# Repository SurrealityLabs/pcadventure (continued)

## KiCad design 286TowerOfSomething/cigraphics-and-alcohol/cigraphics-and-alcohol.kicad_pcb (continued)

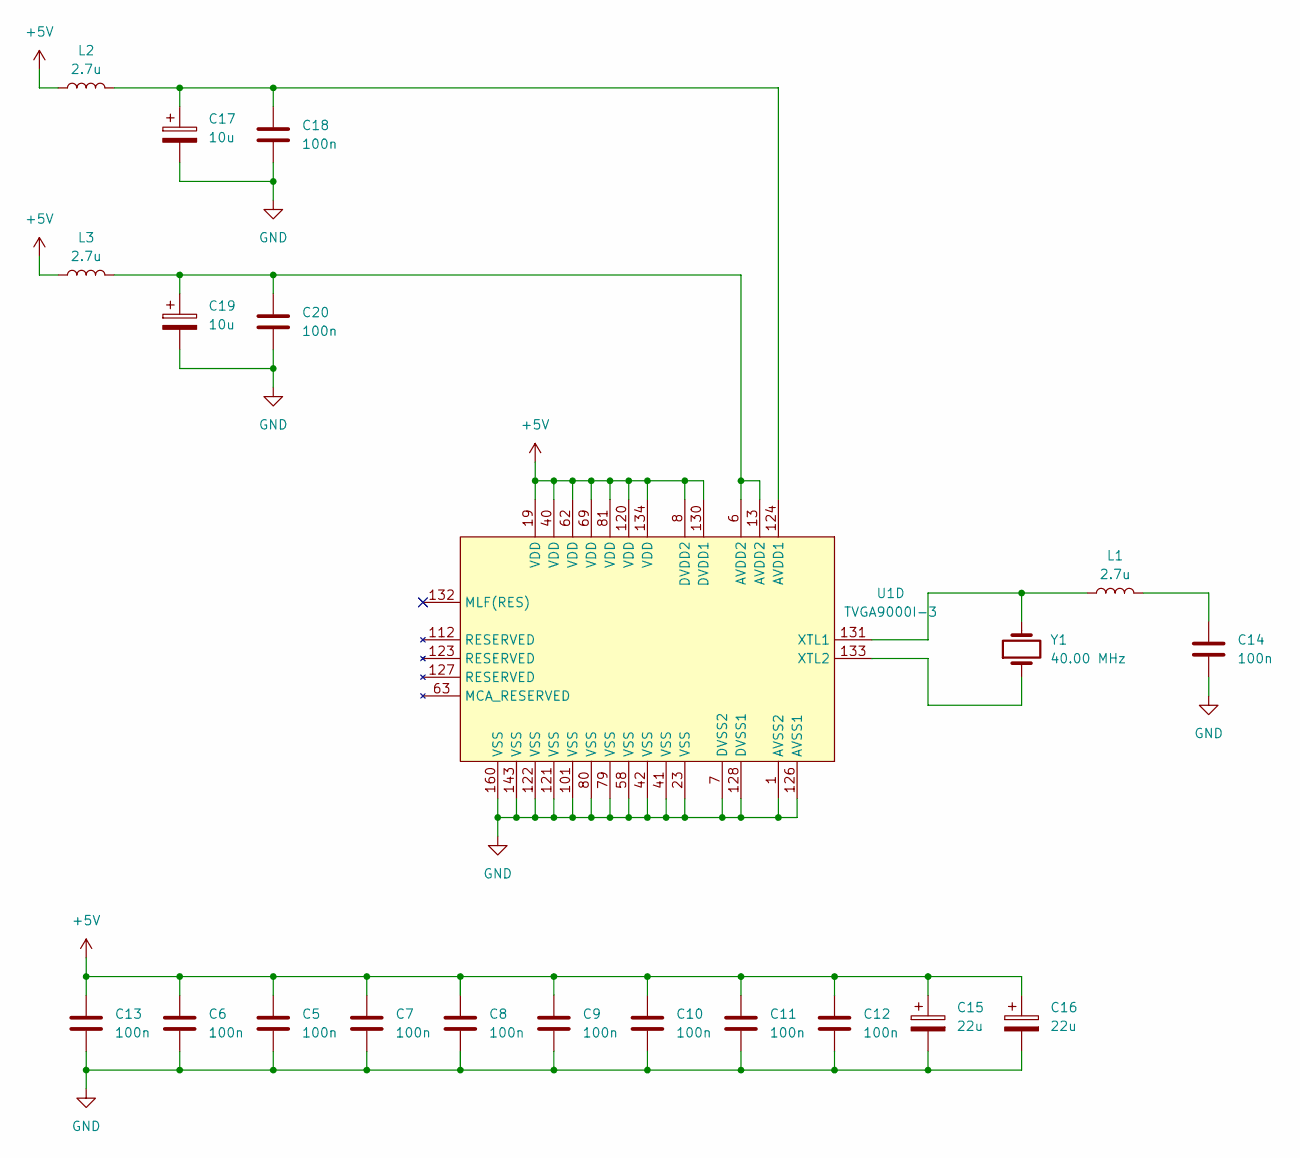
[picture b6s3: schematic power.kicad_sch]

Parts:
C5, C6, C7, C8, C9, C10, C11, C12, C13, C14, C18, C20: 100n; C_0603_1608Metric_Pad1.08x0.95mm_HandSolder
C15, C16: 22u; CP_Elec_5x5.3
C17, C19: 10u; CP_Elec_5x5.3
L1, L2, L3: 2.7u; L_0603_1608Metric_Pad1.05x0.95mm_HandSolder
U1: TVGA9000I-3; PQFP-160_28x28mm_P0.65mm
Y1: 40.00 MHz

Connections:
+5V: C5.1, C6.1, C7.1, C8.1, C9.1, C10.1, C11.1, C12.1, C13.1, C15.1, C16.1, L2.1, L3.1, U1.8 (DVDD2), U1.19 (VDD), U1.40 (VDD), U1.62 (VDD), U1.69 (VDD), U1.81 (VDD), U1.120 (VDD), U1.130 (DVDD1), U1.134 (VDD); also elsewhere on the board
GND: C5.2, C6.2, C7.2, C8.2, C9.2, C10.2, C11.2, C12.2, C13.2, C14.2, C15.2, C16.2, C17.2, C18.2, C19.2, C20.2, U1.1 (AVSS2), U1.7 (DVSS2), U1.23 (VSS), U1.41 (VSS), U1.42 (VSS), U1.58 (VSS), U1.79 (VSS), U1.80 (VSS), U1.101 (VSS), U1.121 (VSS), U1.122 (VSS), U1.126 (AVSS1), U1.128 (DVSS1), U1.143 (VSS), U1.160 (VSS); also elsewhere on the board
unnamed: C14.1, L1.2
unnamed: C19.1, C20.1, L3.2, U1.6 (AVDD2), U1.13 (AVDD2)
unnamed: C17.1, C18.1, L2.2, U1.124 (AVDD1)
unnamed: L1.1, U1.131 (XTL1), Y1.2
unnamed: U1.133 (XTL2), Y1.1

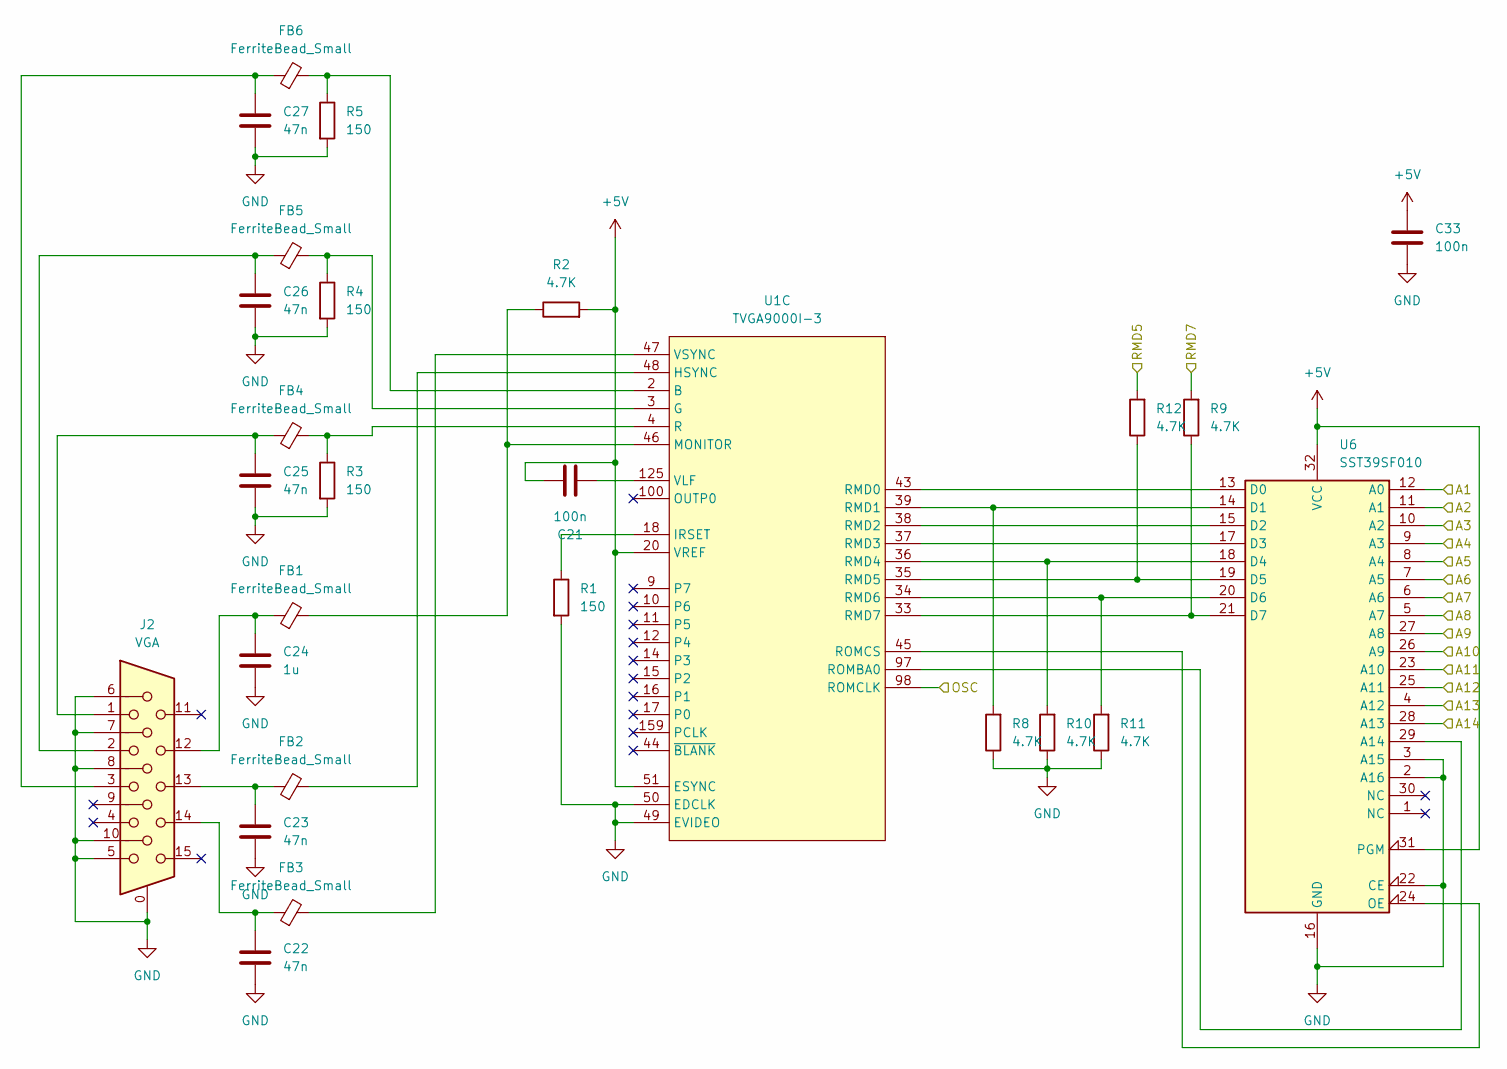
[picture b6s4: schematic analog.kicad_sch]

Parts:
C21, C33: 100n; C_0603_1608Metric_Pad1.08x0.95mm_HandSolder
C22, C23, C25, C26, C27: 47n; C_0603_1608Metric_Pad1.08x0.95mm_HandSolder
C24: 1u; C_0603_1608Metric_Pad1.08x0.95mm_HandSolder
FB1, FB2, FB3, FB4, FB5, FB6: FerriteBead_Small; L_0603_1608Metric_Pad1.05x0.95mm_HandSolder
J2: VGA; DSUB-15-HD_Female_Horizontal_P2.29x1.90mm_EdgePinOffset3.03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
R1, R3, R4, R5: 150; R_0603_1608Metric_Pad0.98x0.95mm_HandSolder
R2, R8, R9, R10, R11, R12: 4.7K; R_0603_1608Metric_Pad0.98x0.95mm_HandSolder
U1: TVGA9000I-3; PQFP-160_28x28mm_P0.65mm
U6: SST39SF010; DIP-32_W15.24mm

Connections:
+5V: C21.2, C33.1, R2.2, U1.20 (VREF), U1.51 (ESYNC), U6.31 (PGM), U6.32 (VCC); also elsewhere on the board
/A1: U6.12 (A0); also elsewhere on the board
/A2: U6.11 (A1); also elsewhere on the board
/A3: U6.10 (A2); also elsewhere on the board
/A4: U6.9 (A3); also elsewhere on the board
/A5: U6.8 (A4); also elsewhere on the board
/A6: U6.7 (A5); also elsewhere on the board
/A7: U6.6 (A6); also elsewhere on the board
/A8: U6.5 (A7); also elsewhere on the board
/A9: U6.27 (A8); also elsewhere on the board
/A10: U6.26 (A9); also elsewhere on the board
/A11: U6.23 (A10); also elsewhere on the board
/A12: U6.25 (A11); also elsewhere on the board
/A13: U6.4 (A12); also elsewhere on the board
/A14: U6.28 (A13); also elsewhere on the board
/Analog/RMD5: R12.2; also elsewhere on the board
/Analog/RMD7: R9.2; also elsewhere on the board
/OSC: U1.98 (ROMCLK); also elsewhere on the board
GND: C22.2, C23.2, C24.2, C25.2, C26.2, C27.2, C33.2, J2.0, J2.5, J2.6, J2.7, J2.8, J2.10, R1.2, R3.2, R4.2, R5.2, R8.1, R10.1, R11.1, U1.49 (EVIDEO), U1.50 (EDCLK), U6.2 (A16), U6.3 (A15), U6.16 (GND), U6.22 (CE); also elsewhere on the board
unnamed: C22.1, FB3.1, J2.14
unnamed: C23.1, FB2.1, J2.13
unnamed: C24.1, FB1.1, J2.12
unnamed: C25.1, FB4.1, J2.1
unnamed: C26.1, FB5.1, J2.2
unnamed: C27.1, FB6.1, J2.3
unnamed: FB6.2, R5.1, U1.2 (B)
unnamed: FB5.2, R4.1, U1.3 (G)
unnamed: FB2.2, U1.48 (HSYNC)
unnamed: R1.1, U1.18 (IRSET)
unnamed: FB1.2, R2.1, U1.46 (MONITOR)
unnamed: FB4.2, R3.1, U1.4 (R)
unnamed: U1.43 (RMD0), U6.13 (D0)
unnamed: R8.2, U1.39 (RMD1), U6.14 (D1)
unnamed: U1.38 (RMD2), U6.15 (D2)
unnamed: U1.37 (RMD3), U6.17 (D3)
unnamed: R10.2, U1.36 (RMD4), U6.18 (D4)
unnamed: R12.1, U1.35 (RMD5), U6.19 (D5)
unnamed: R11.2, U1.34 (RMD6), U6.20 (D6)
unnamed: R9.1, U1.33 (RMD7), U6.21 (D7)
unnamed: U1.97 (ROMBA0), U6.29 (A14)
unnamed: U1.45 (ROMCS), U6.24 (OE)
unnamed: C21.1, U1.125 (VLF)
unnamed: FB3.2, U1.47 (VSYNC)

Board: 2 copper layers, 70 parts (0 on the bottom side), 130 nets, no tracks yet.

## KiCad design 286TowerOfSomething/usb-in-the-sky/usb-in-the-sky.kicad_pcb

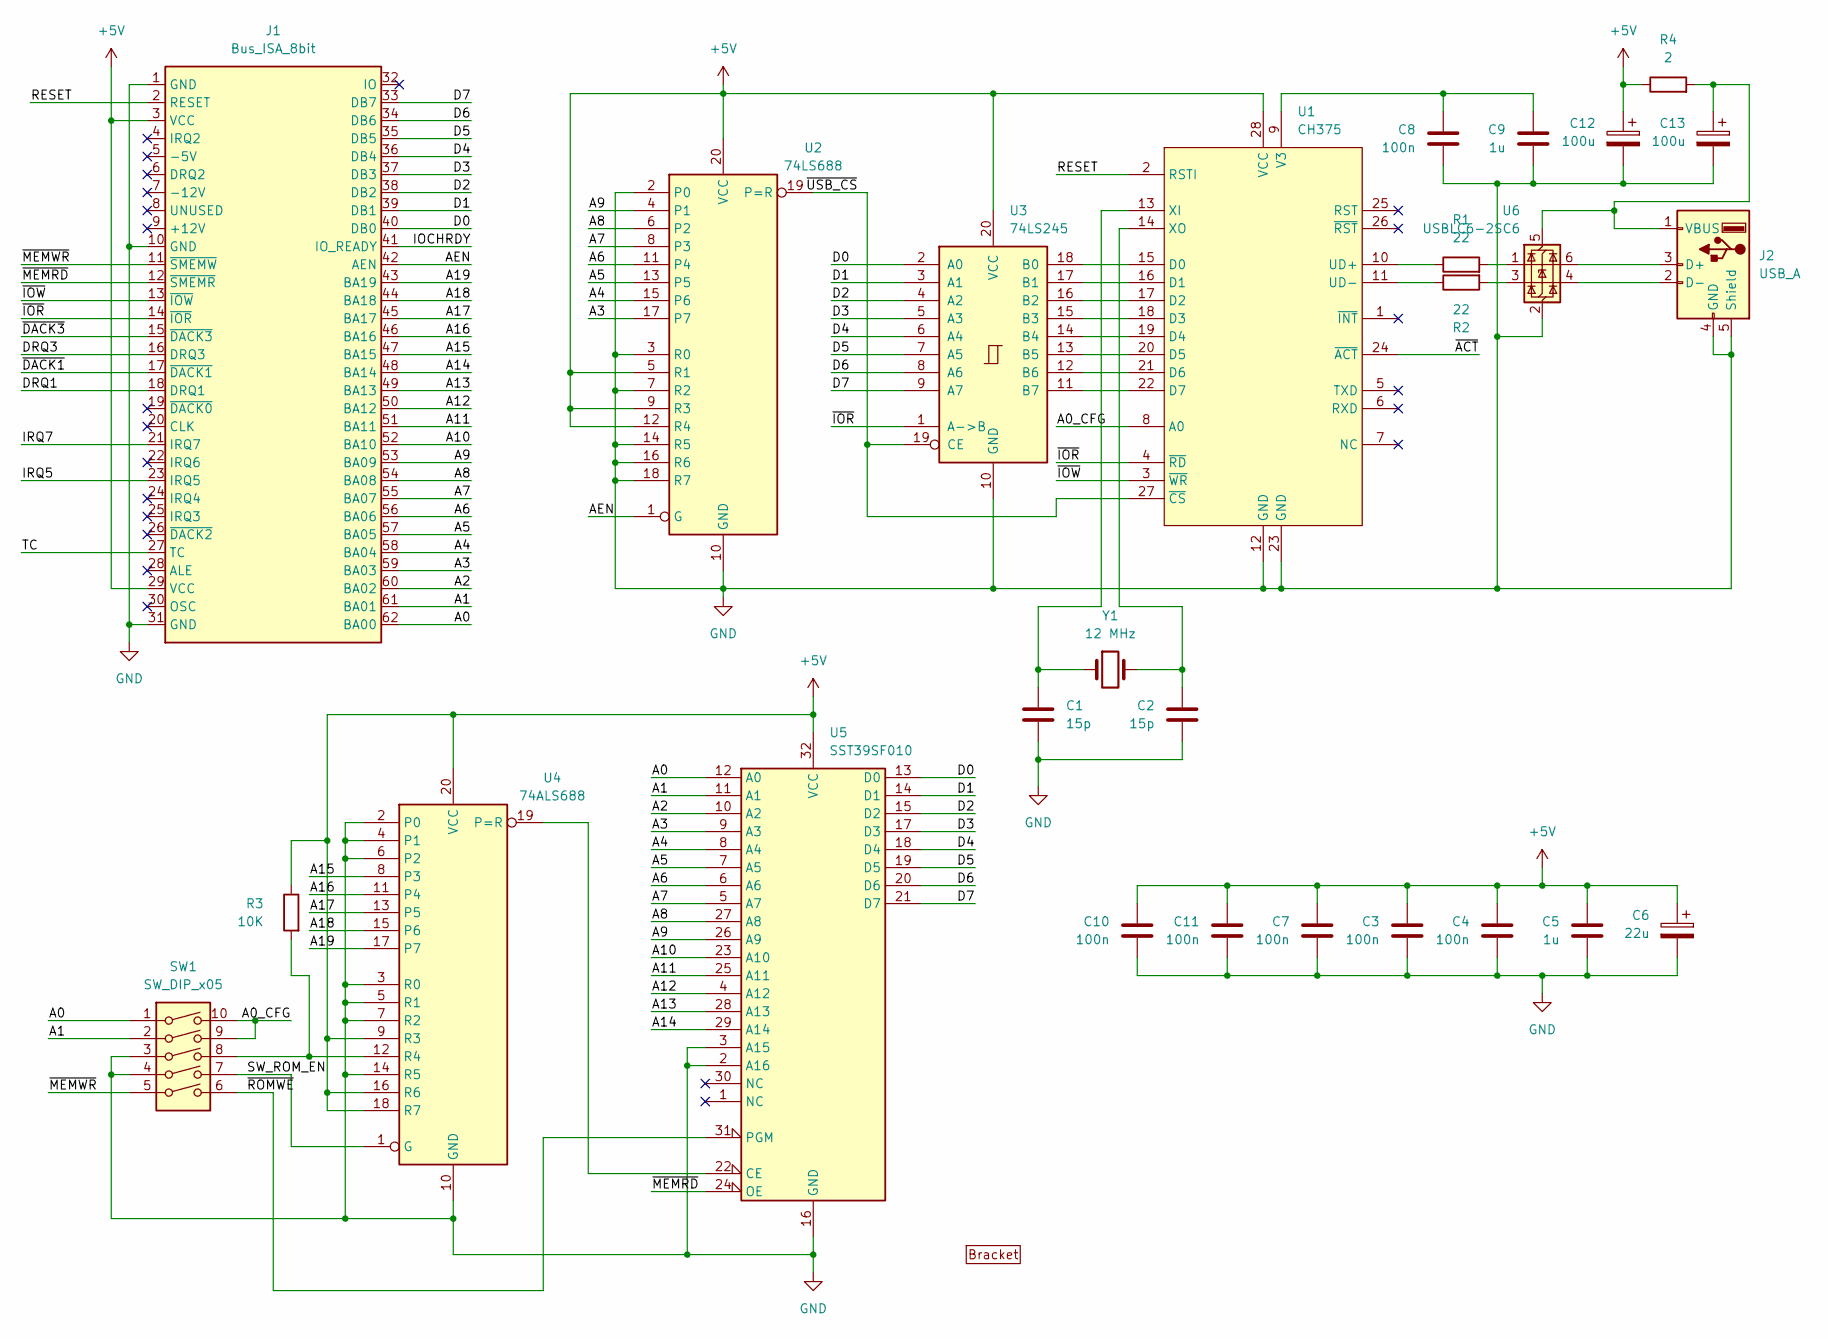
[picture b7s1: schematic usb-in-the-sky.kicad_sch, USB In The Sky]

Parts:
BRACKET1: PC_BRACKET_ISA_KEYSTONE_9200_Rev1_1
C1, C2: 15p; C_0603_1608Metric_Pad1.08x0.95mm_HandSolder
C3, C4, C7, C8, C10, C11: 100n; C_0603_1608Metric_Pad1.08x0.95mm_HandSolder
C5, C9: 1u; C_0805_2012Metric_Pad1.18x1.45mm_HandSolder
C6: 22u; CP_Elec_5x5.3
C12, C13: 100u; CP_Elec_5x5.3
J1: Bus_ISA_8bit; BUS_AT_8BIT
J2: USB_A; USB_A_Stewart_SS-52100-001_Horizontal
R1, R2: 22; R_0603_1608Metric_Pad0.98x0.95mm_HandSolder
R3: 10K; R_0603_1608Metric_Pad0.98x0.95mm_HandSolder
R4: 2; R_0603_1608Metric_Pad0.98x0.95mm_HandSolder
SW1: SW_DIP_x05; SW_DIP_SPSTx05_Slide_9.78x14.88mm_W7.62mm_P2.54mm
U1: CH375; SOP-28_8.4x18.16mm_P1.27mm
U2: 74LS688; DIP-20_W7.62mm
U3: 74LS245; DIP-20_W7.62mm
U4: 74ALS688; DIP-20_W7.62mm
U5: SST39SF010; DIP-32_W15.24mm
U6: USBLC6-2SC6; SOT-23-6
Y1: 12 MHz; Crystal_HC49-U_Vertical

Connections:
+5V: C3.1, C4.1, C5.1, C6.1, C7.1, C10.1, C11.1, C12.1, J1.3 (VCC), J1.29 (VCC), R3.1, R4.1, U1.28 (VCC), U2.5 (R1), U2.9 (R3), U2.12 (R4), U2.20 (VCC), U3.20 (VCC), U4.9 (R3), U4.16 (R6), U4.18 (R7), U4.20 (VCC), U5.32 (VCC)
/A0: J1.62 (BA00), SW1.1, U5.12 (A0)
/A0_CFG: SW1.9, SW1.10, U1.8 (A0)
/A1: J1.61 (BA01), SW1.2, U5.11 (A1)
/A2: J1.60 (BA02), U5.10 (A2)
/A3: J1.59 (BA03), U2.17 (P7), U5.9 (A3)
/A4: J1.58 (BA04), U2.15 (P6), U5.8 (A4)
/A5: J1.57 (BA05), U2.13 (P5), U5.7 (A5)
/A6: J1.56 (BA06), U2.11 (P4), U5.6 (A6)
/A7: J1.55 (BA07), U2.8 (P3), U5.5 (A7)
/A8: J1.54 (BA08), U2.6 (P2), U5.27 (A8)
/A9: J1.53 (BA09), U2.4 (P1), U5.26 (A9)
/A10: J1.52 (BA10), U5.23 (A10)
/A11: J1.51 (BA11), U5.25 (A11)
/A12: J1.50 (BA12), U5.4 (A12)
/A13: J1.49 (BA13), U5.28 (A13)
/A14: J1.48 (BA14), U5.29 (A14)
/A15: J1.47 (BA15), U4.8 (P3)
/A16: J1.46 (BA16), U4.11 (P4)
/A17: J1.45 (BA17), U4.13 (P5)
/A18: J1.44 (BA18), U4.15 (P6)
/A19: J1.43 (BA19), U4.17 (P7)
/AEN: J1.42 (AEN), U2.1 (G)
/D0: J1.40 (DB0), U3.2 (A0), U5.13 (D0)
/D1: J1.39 (DB1), U3.3 (A1), U5.14 (D1)
/D2: J1.38 (DB2), U3.4 (A2), U5.15 (D2)
/D3: J1.37 (DB3), U3.5 (A3), U5.17 (D3)
/D4: J1.36 (DB4), U3.6 (A4), U5.18 (D4)
/D5: J1.35 (DB5), U3.7 (A5), U5.19 (D5)
/D6: J1.34 (DB6), U3.8 (A6), U5.20 (D6)
/D7: J1.33 (DB7), U3.9 (A7), U5.21 (D7)
/DRQ1: J1.18 (DRQ1)
/DRQ3: J1.16 (DRQ3)
/IOCHRDY: J1.41 (IO_READY)
/IRQ5: J1.23 (IRQ5)
/IRQ7: J1.21 (IRQ7)
/RESET: J1.2 (RESET), U1.2 (RSTI)
/SW_ROM_EN: SW1.7, U4.1 (G)
/TC: J1.27 (TC)
/~ACT: U1.24 (~ACT)
/~DACK1: J1.17 (~DACK1)
/~DACK3: J1.15 (~DACK3)
/~IOR: J1.14 (~IOR), U1.4 (~RD), U3.1 (A->B)
/~IOW: J1.13 (~IOW), U1.3 (~WR)
/~MEMRD: J1.12 (~SMEMR), U5.24 (OE)
/~MEMWR: J1.11 (~SMEMW), SW1.5
/~ROMWE: SW1.6, U5.31 (PGM)
/~USB_CS: U1.27 (~CS), U2.19 (P=R), U3.19 (CE)
GND: C1.2, C2.2, C3.2, C4.2, C5.2, C6.2, C7.2, C8.2, C9.2, C10.2, C11.2, C12.2, C13.2, J1.1 (GND), J1.10 (GND), J1.31 (GND), J2.4 (GND), J2.5 (Shield), SW1.3, SW1.4, U1.12 (GND), U1.23 (GND), U2.2 (P0), U2.3 (R0), U2.7 (R2), U2.10 (GND), U2.14 (R5), U2.16 (R6), U2.18 (R7), U3.10 (GND), U4.2 (P0), U4.3 (R0), U4.4 (P1), U4.5 (R1), U4.6 (P2), U4.7 (R2), U4.10 (GND), U4.14 (R5), U5.2 (A16), U5.3 (A15), U5.16 (GND), U6.2 (GND)
unnamed: J2.3 (D+), U6.6 (I/O1)
unnamed: J2.2 (D-), U6.4 (I/O2)
unnamed: C13.1, J2.1 (VBUS), R4.2, U6.5 (VBUS)
unnamed: R1.2, U6.1 (I/O1)
unnamed: R2.2, U6.3 (I/O2)
unnamed: U1.15 (D0), U3.18 (B0)
unnamed: U1.16 (D1), U3.17 (B1)
unnamed: U1.17 (D2), U3.16 (B2)
unnamed: U1.18 (D3), U3.15 (B3)
unnamed: U1.19 (D4), U3.14 (B4)
unnamed: U1.20 (D5), U3.13 (B5)
unnamed: U1.21 (D6), U3.12 (B6)
unnamed: U1.22 (D7), U3.11 (B7)
unnamed: R1.1, U1.10 (UD+)
unnamed: R2.1, U1.11 (UD-)
unnamed: C8.1, C9.1, U1.9 (V3)
unnamed: C1.1, U1.13 (XI), Y1.1
unnamed: C2.1, U1.14 (XO), Y1.2
unnamed: U4.19 (P=R), U5.22 (CE)
unnamed: R3.2, SW1.8, U4.12 (R4)

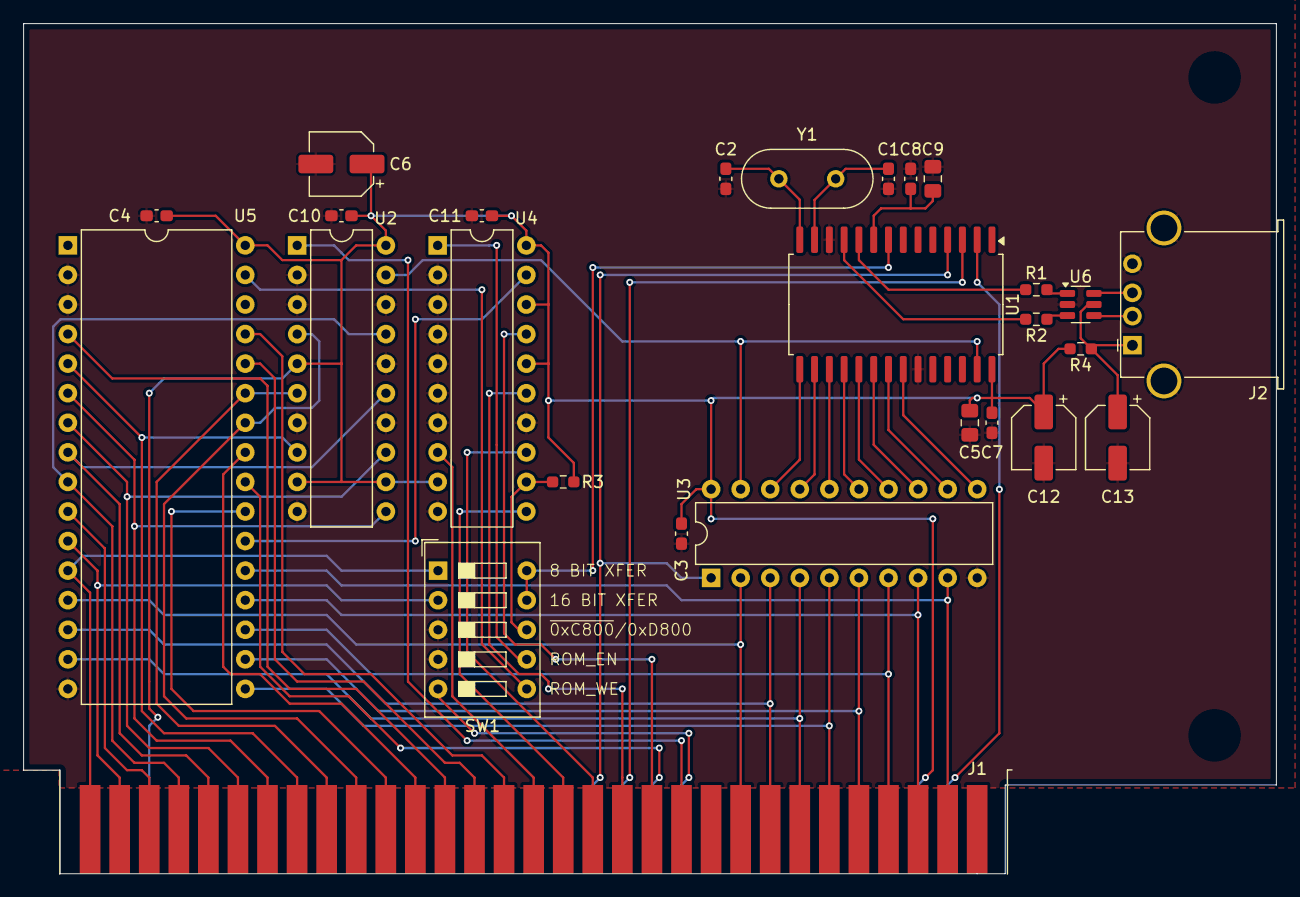
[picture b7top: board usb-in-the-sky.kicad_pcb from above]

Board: 2 copper layers, 107.6 x 73.0 mm, 28 parts (0 on the bottom side), 60 nets.

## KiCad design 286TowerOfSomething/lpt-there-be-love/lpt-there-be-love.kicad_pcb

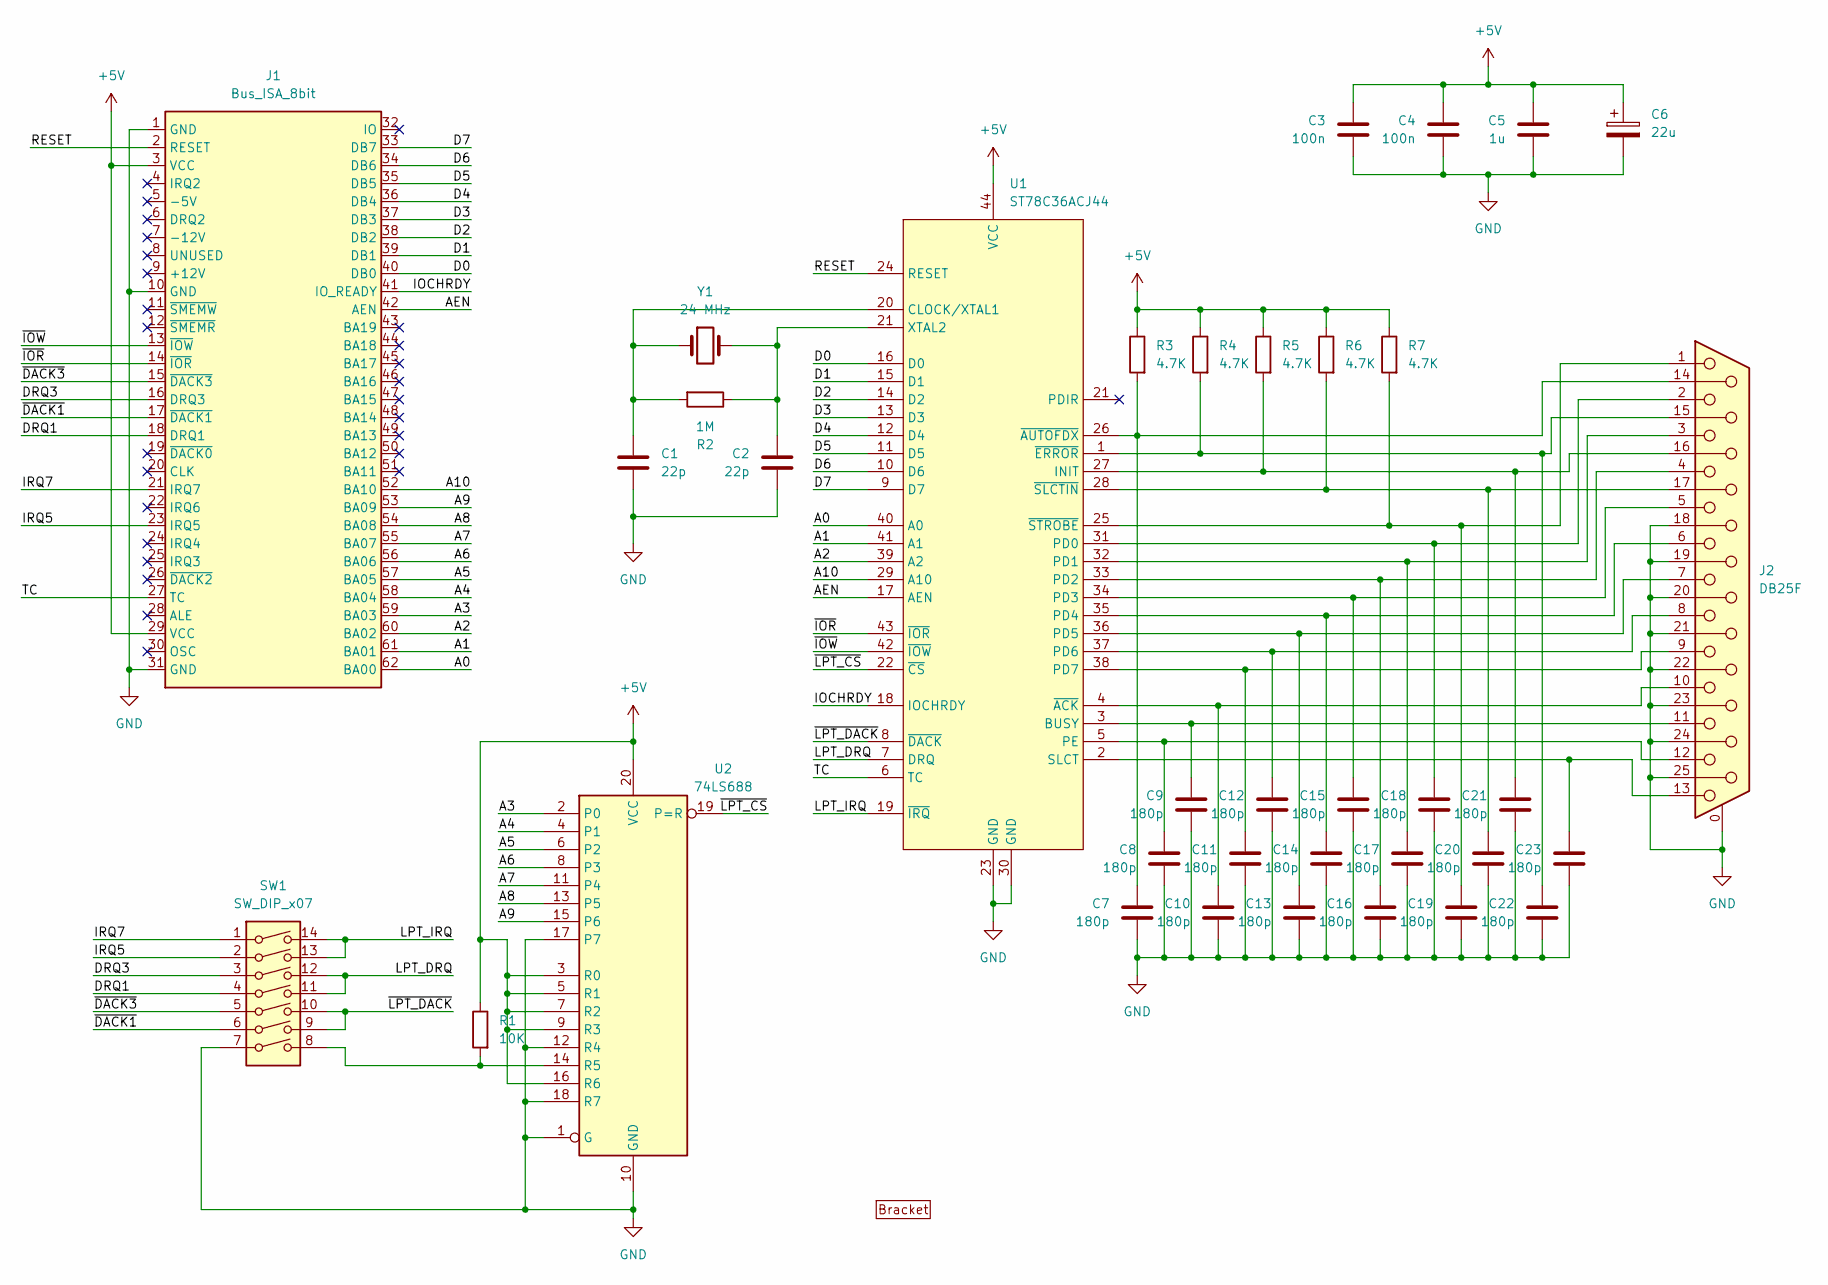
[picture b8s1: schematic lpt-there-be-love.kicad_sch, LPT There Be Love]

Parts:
BRACKET1: PC_BRACKET_ISA_KEYSTONE_9200_Rev1_1
C1, C2: 22p; C_0603_1608Metric_Pad1.08x0.95mm_HandSolder
C3, C4: 100n; C_0603_1608Metric_Pad1.08x0.95mm_HandSolder
C5: 1u; C_0805_2012Metric_Pad1.18x1.45mm_HandSolder
C6: 22u; CP_Elec_5x5.3
C7, C8, C9, C10, C11, C12, C13, C14, C15, C16, C17, C18, C19, C20, C21, C22, C23: 180p; C_0603_1608Metric_Pad1.08x0.95mm_HandSolder
J1: Bus_ISA_8bit; BUS_AT_8BIT
J2: DB25F; DSUB-25_Female_Horizontal_P2.77x2.84mm_EdgePinOffset4.94mm_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
R1: 10K; R_0603_1608Metric_Pad0.98x0.95mm_HandSolder
R2: 1M; R_0603_1608Metric_Pad0.98x0.95mm_HandSolder
R3, R4, R5, R6, R7: 4.7K; R_0603_1608Metric_Pad0.98x0.95mm_HandSolder
SW1: SW_DIP_x07; SW_DIP_SPSTx07_Slide_9.78x19.96mm_W7.62mm_P2.54mm
U1: ST78C36ACJ44; PLCC-44_THT-Socket
U2: 74LS688; DIP-20_W7.62mm
Y1: 24 MHz; Crystal_HC49-U_Vertical

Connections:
+5V: C3.1, C4.1, C5.1, C6.1, J1.3 (VCC), J1.29 (VCC), R1.1, R3.1, R4.1, R5.1, R6.1, R7.1, U1.44 (VCC), U2.3 (R0), U2.5 (R1), U2.7 (R2), U2.9 (R3), U2.16 (R6), U2.20 (VCC)
/A0: J1.62 (BA00), U1.40 (A0)
/A1: J1.61 (BA01), U1.41 (A1)
/A2: J1.60 (BA02), U1.39 (A2)
/A3: J1.59 (BA03), U2.2 (P0)
/A4: J1.58 (BA04), U2.4 (P1)
/A5: J1.57 (BA05), U2.6 (P2)
/A6: J1.56 (BA06), U2.8 (P3)
/A7: J1.55 (BA07), U2.11 (P4)
/A8: J1.54 (BA08), U2.13 (P5)
/A9: J1.53 (BA09), U2.15 (P6)
/A10: J1.52 (BA10), U1.29 (A10)
/AEN: J1.42 (AEN), U1.17 (AEN)
/D0: J1.40 (DB0), U1.16 (D0)
/D1: J1.39 (DB1), U1.15 (D1)
/D2: J1.38 (DB2), U1.14 (D2)
/D3: J1.37 (DB3), U1.13 (D3)
/D4: J1.36 (DB4), U1.12 (D4)
/D5: J1.35 (DB5), U1.11 (D5)
/D6: J1.34 (DB6), U1.10 (D6)
/D7: J1.33 (DB7), U1.9 (D7)
/DRQ1: J1.18 (DRQ1), SW1.4
/DRQ3: J1.16 (DRQ3), SW1.3
/IOCHRDY: J1.41 (IO_READY), U1.18 (IOCHRDY)
/IRQ5: J1.23 (IRQ5), SW1.2
/IRQ7: J1.21 (IRQ7), SW1.1
/LPT_DRQ: SW1.11, SW1.12, U1.7 (DRQ)
/LPT_IRQ: SW1.13, SW1.14, U1.19 (~IRQ)
/RESET: J1.2 (RESET), U1.24 (RESET)
/TC: J1.27 (TC), U1.6 (TC)
/~DACK1: J1.17 (~DACK1), SW1.6
/~DACK3: J1.15 (~DACK3), SW1.5
/~IOR: J1.14 (~IOR), U1.43 (~IOR)
/~IOW: J1.13 (~IOW), U1.42 (~IOW)
/~LPT_CS: U1.22 (~CS), U2.19 (P=R)
/~LPT_DACK: SW1.9, SW1.10, U1.8 (~DACK)
GND: C1.2, C2.2, C3.2, C4.2, C5.2, C6.2, C7.2, C8.2, C9.2, C10.2, C11.2, C12.2, C13.2, C14.2, C15.2, C16.2, C17.2, C18.2, C19.2, C20.2, C21.2, C22.2, C23.2, J1.1 (GND), J1.10 (GND), J1.31 (GND), J2.0 (PAD), J2.18, J2.19, J2.20, J2.21, J2.22, J2.23, J2.24, J2.25, SW1.7, U1.23 (GND), U1.30 (GND), U2.1 (G), U2.10 (GND), U2.12 (R4), U2.17 (P7), U2.18 (R7)
unnamed: C7.1, J2.14, R3.2, U1.26 (~AUTOFDX)
unnamed: C22.1, J2.15, R4.2, U1.1 (~ERROR)
unnamed: C21.1, J2.16, R5.2, U1.27 (INIT)
unnamed: C20.1, J2.17, R6.2, U1.28 (~SLCTIN)
unnamed: C9.1, J2.11, U1.3 (BUSY)
unnamed: C1.1, R2.2, U1.20 (CLOCK/XTAL1), Y1.1
unnamed: C18.1, J2.2, U1.31 (PD0)
unnamed: C17.1, J2.3, U1.32 (PD1)
unnamed: C16.1, J2.4, U1.33 (PD2)
unnamed: C15.1, J2.5, U1.34 (PD3)
unnamed: C14.1, J2.6, U1.35 (PD4)
unnamed: C13.1, J2.7, U1.36 (PD5)
unnamed: C12.1, J2.8, U1.37 (PD6)
unnamed: C11.1, J2.9, U1.38 (PD7)
unnamed: C8.1, J2.12, U1.5 (PE)
unnamed: C23.1, J2.13, U1.2 (SLCT)
unnamed: C2.1, R2.1, U1.21 (XTAL2), Y1.2
unnamed: C10.1, J2.10, U1.4 (~ACK)
unnamed: C19.1, J2.1, R7.2, U1.25 (~STROBE)
unnamed: R1.2, SW1.8, U2.14 (R5)

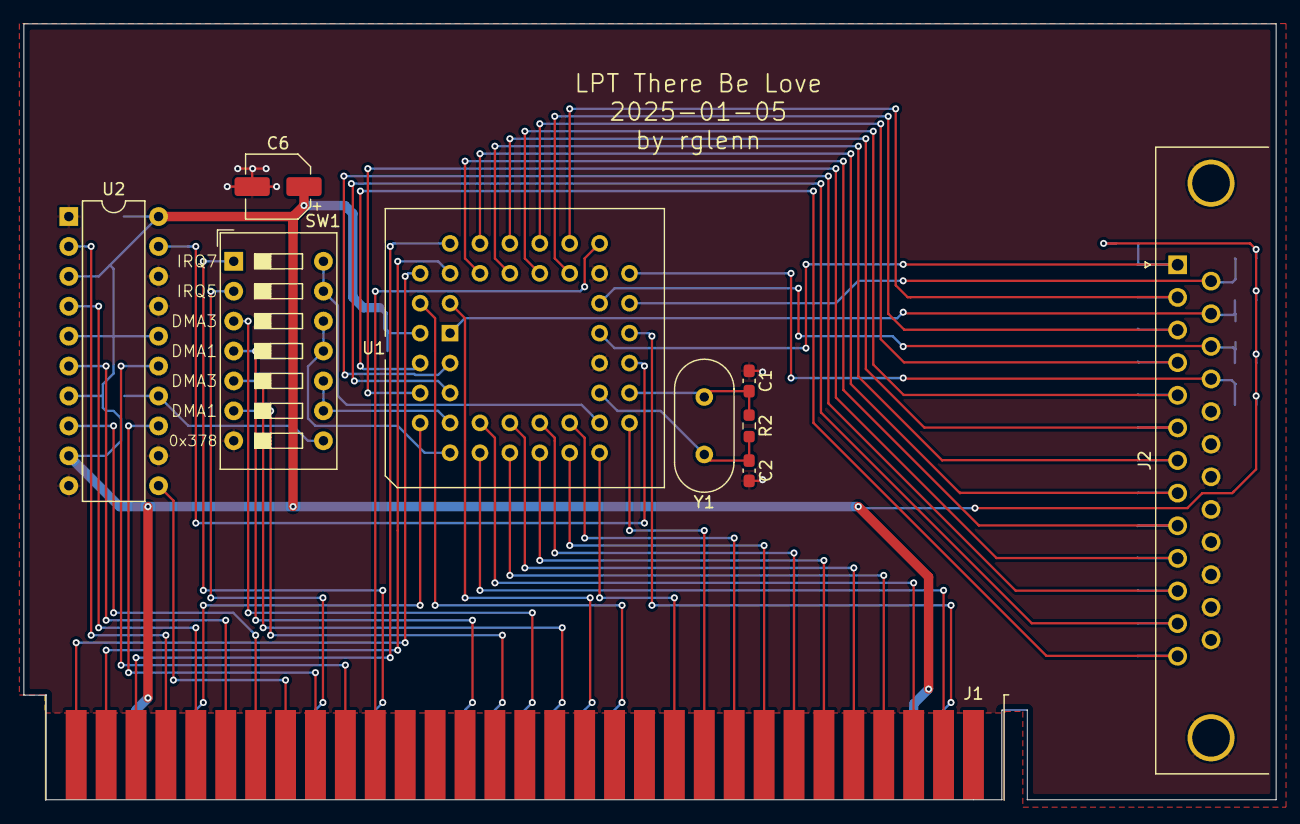
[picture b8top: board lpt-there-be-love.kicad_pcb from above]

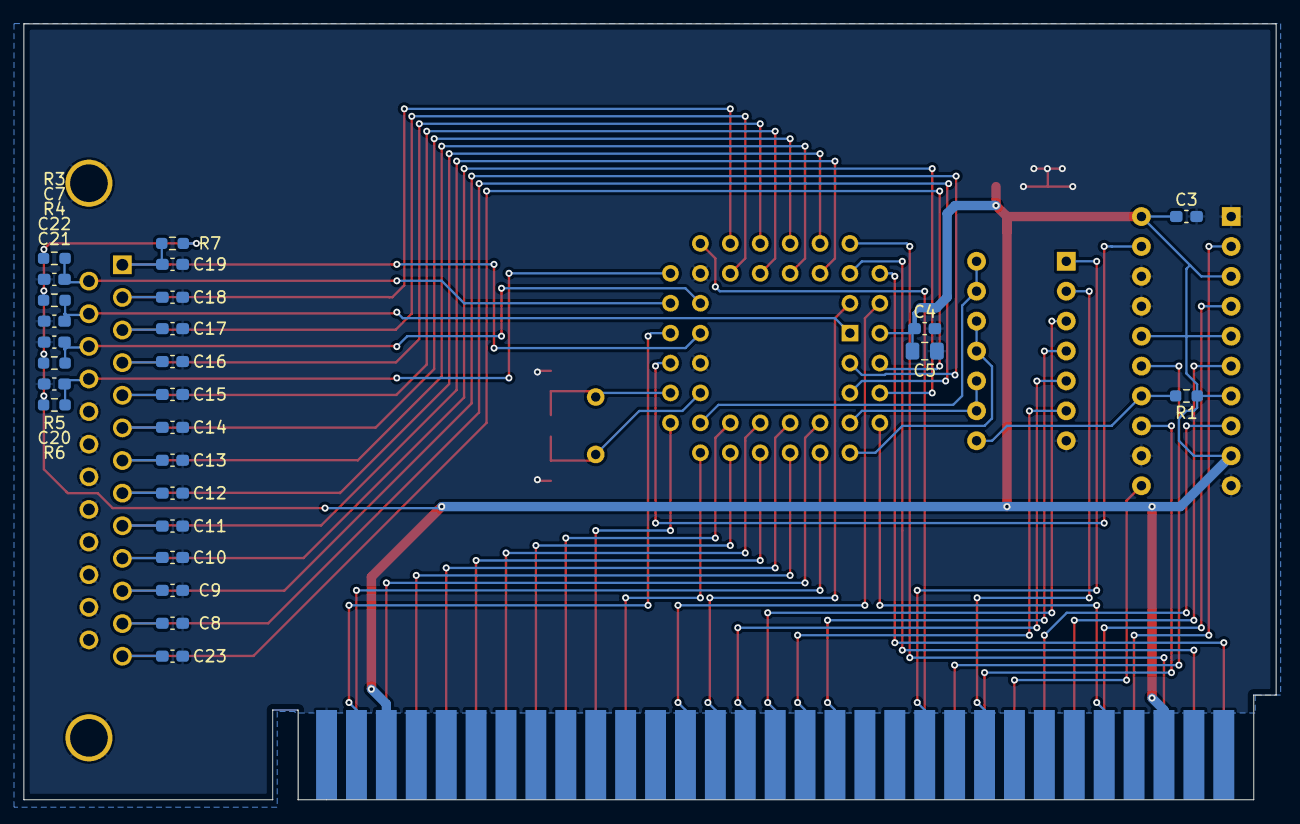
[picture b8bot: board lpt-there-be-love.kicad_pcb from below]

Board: 2 copper layers, 106.3 x 65.9 mm, 37 parts (26 on the bottom side), 57 nets.

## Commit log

2024-08-14 Adding datasheet for 286 SCAT Chipset
2024-08-14 Adding README
2024-08-14 Adding the rest of the research material so far
2024-08-14 Update README.md
    Fixing formatting
2024-08-14 Adding plan for the system
2024-08-16 Started adding subprojects. IDE card is 75% schematic complete.
2024-08-17 Schematic for compagne-supernova at like 50%
2024-08-18 Started adding custom symbols and footprints. Schematic basically complete for flop-tonight
2024-08-18 Finished schematic of compagne-supernova. Started messing with layout.
2024-08-18 Adding datasheet of the floppy controller we're actually using
2024-08-18 Finishing schematic of the-importance-of-being-ide
2024-08-18 Adding link to firmware for ATTiny85 to convert PS/2 mouse to Serial
2024-08-21 lpt-there-be-love schematic is at about 85% - added parport ASIC symbol and most of the schematic was doneat that point
2024-08-22 Adding more docs and examples for 386 and 486
2024-08-22 Added schematic of ethermaker at like 95%
2024-08-22 Adding updated parts library missing from last commit
2024-08-22 Adding datasheet for flash chip
2024-08-23 Added symbol for 286 CPU, and associated datasheet
2024-08-23 Started defining footprints for F82C235 286 chipset and 80C237 FPU
2024-08-23 Adding docs and inital symbol/schematic work for CS4237B-based soundcard supersonic
2024-08-25 Adding 287 datasheet
2024-08-25 Adding M6117C schematic
2024-08-27 Finishing CS4237B symbol
2024-09-02 Started on schematic for sound card
2024-09-04 Laying out 80287 symbol
2024-09-05 Making symbol table entries relative instead of absolute
2024-09-05 Switching footprint libraries to also use a relative path
2024-09-05 Finishing symbol for SCAT chipset
2024-09-06 Adding datasheet and schematic symbol for 8242 keyboard IC
2024-09-07 Adding drivers for the Ethernet card
2024-09-08 Adding schematic for M6117D-based video server
2024-09-11 Added symbol for RAM chip, and datasheet
2024-09-11 Started adding more parts to 286 card
2024-09-11 Adding initial work on 386 CPU card
2024-09-12 Adding docs for 386 C PUs, 386 motherboards, and TVGA9000i VGA chip
2024-09-12 Figuring out more of the M6117C pins from the M6117D datasheet, and 386 chipset and CPU datasheets
2024-09-13 Found a whole bunch of relevant schematics and docs for the M6117D on Internet Archive
2024-09-14 Adding M6117 product brief for the heck of it
2024-09-17 Started working on M6117C schematic symbol
2024-09-18 M6117C symbol is in reasonable shape
2024-09-19 Adding labels to units
2024-09-21 Started board layout for lpt-there-be-love
2024-09-22 Added start of rom-n-roll-star
2024-09-22 Finished routing?
2024-09-23 Layout of lpt-there-be-love just about done
2024-09-24 Started adding docs and symbol for CH375
2024-09-24 Adding first stab at schematic for usb-in-the-sky
2024-09-25 Renaming dmp-look-back-in-anger to dmp-go-away
2024-09-25 Reserving dont-look-backplane-in-anger for backplane
2024-09-25 Reserving name for 486 board, acquisis
2024-09-28 Adding silkscreen to rom-n-roll-star
2024-09-28 Adding footprints to everything in usb-in-the-sky
2024-09-29 Doing some work on the compagne-supernova layout
2024-09-30 Adding first work on TVGA900i symbol
2024-09-30 Fixing some pins on the wrong unit
2024-10-01 Added name for cigraphics-and-alcohol, and finished symbol for TVGA9000i
2024-10-03 Starting on schematic for VGA card
2024-10-04 Adding symbol for MCM514256AP70 DRAM
2024-10-04 Adding RAM to cigraphics-and-alcohol
2024-10-05 Almost finished schematic for cigraphics-and-alcohol
2024-10-05 Adding datasheet for DRAM for video card, and fixing CAS and RAS on video card
2024-10-06 I swear bro, just one more cap...
2024-10-07 Started on schematic for dmp-go-away
2024-10-08 Adding work done on 386 card, coming along nicely
2024-10-08 Adding schematic of serial + parallel card using TL16C552A
2024-10-09 Adding keyboard/mouse and oscillator to schematic of dmp-go-away
2024-10-10 Adding some missing caps, and the optional DS12885 RTC for dmp-go-away
2024-10-10 Started adding TL16C552A symbol and docs
2024-10-11 Moving extra NC X
2024-10-12 Adding go-lpt-it-out, a combination serial and parallel card
2024-10-13 Adding spec for position of IO plate attachment points
2024-10-14 Some work on the flop-tonight layout
2024-10-16 More schematic work on go-lpt-it-out
2024-10-17 Adding address decoding spreadsheet
2024-10-19 Adding TVGA8900D datasheet to reverse engineer that card
2024-10-19 Added footprints and started figuring out layout for dmp-go-away
2024-10-19 Adding footprint for RAM. Needs updates.
2024-10-20 More work on dont-look-backplane-in-anger
2024-10-21 Adding an eighth slot to the backplane
2024-10-22 Adding inverter on RESET line to go-lpt-it-out
2024-12-04 More work on layout
2024-12-05 More layout work on go-lpt-it-out
2024-12-07 Most of the layout done except for the power
2024-12-08 Started on layout for ethermaker
2024-12-08 Layout for Flop Tonight is complete. Needs adjustment to fit a bracket properly.
2024-12-08 Added a board edge to go-lpt-it-out and almost finished routing
2024-12-10 Started work on IDE layout
2024-12-11 More layout work.
2024-12-11 Started working on usb-in-the-sky layout
2024-12-12 More layout work on usb-in-the-sky
2024-12-13 Layout done?
2024-12-14 Shrinking board
2024-12-15 Work on USB in the Sky silkscreen
2024-12-16 Work on ethermaker layout
2024-12-16 I think that's an Ethernet carD
2024-12-17 Cleaning up silkscreen
2024-12-19 Cleaned up schematic, broke layout
2024-12-19 Revert "Cleaned up schematic, broke layout"
    This reverts commit 42e2edff88598cae901a53fb2aea1a81c84d528d.
2024-12-21 Ripping up traces, I'm rethinking the layout
2024-12-21 More work on layout of IDE card
2024-12-21 Schematic corrections, and layout almost done
2024-12-22 Last trace put in
2024-12-24 Started on silkscreen for lpt-there-be-love
2025-01-02 Adding template for 16-bit ISA card with bracket
2025-01-03 Adding template for 8-bit card
2025-01-03 Adding 3D models for ISA brackets
2025-01-04 Adding ISA card template with one DB9 connector
2025-01-05 Adding Keystone 9200 bracket, and fixing refdes on no-port ISA card
2025-01-06 Fixing refdes on one db9 card template
2025-01-07 Updating 8-bit template to fix refdes
2025-01-08 Adding two DB9 ISA template
2025-01-09 Adding one DB25 ISA card template
2025-01-10 Adding template for ISA card with DB9 and DB25
2025-01-11 Adding ISA bracked to rom-n-roll-star
2025-01-12 Adding proper bracket to lpt-there-be-love
2025-01-13 Adding bracket to The Importance of Being IDE
2025-01-14 Updating go-lpt-it-out with bracket
2025-01-15 Adding bracket to USB card
2025-01-16 Adding bracket to graphics card
2025-01-17 Adding bracket to ethernet adapter
2025-01-18 Adding bracket to dmp-go-away
2025-01-18 Adding list of systems to build
2025-01-19 Adding template to sound card:
2025-01-19 Moving files out of 286 folder and into root, for ROM card
2025-01-19 Moving libraries and docs to root
2025-01-20 Moving SiS card in progress
2025-01-20 Moving USB card
2025-01-20 Moving ISA card templates
2025-01-21 Moving go-lpt-it-out
2025-01-22 Moving flop-tonight
2025-01-23 Moving lpt-there-be-love
2025-01-24 Moving compagne-supernova
2025-01-25 Moving cigraphics-and-alcohol
2025-01-25 Moving Ethernet stuff
2025-01-26 Moving backplane
2025-01-27 Moving IDE card
2025-01-28 Moving supersonic
2025-01-28 Adding change to backplane project file
2025-01-29 Moving plan file and scat-no-shadow
2025-01-30 Moving dmp-go-away
2025-04-17 Adding layout of dmp-go-away in progress
2025-05-01 Adding IDE fixes and some layout work
2025-05-01 Adding ethermaker board updates
2025-05-01 Adding flop-tonight updates
2025-05-01 Adding updates to go-lpt-it-out
2025-05-01 Adding last-minute changes to rom-n-roll-star
2025-05-01 Updating systems list
2025-05-01 Adding last minute changes to the-importance-of-being-ide
2025-05-01 Adding latest updates to usb-in-the-sky
2025-05-01 Adding most recent updates to scat-no-shadow
2025-05-30 Adding modified Sergey Kiselev backplane, updated for KiCAD 9 and incorporating a GAL-based POST code decoder
2025-05-31 Updating footprint and 3D model for ISA slots
